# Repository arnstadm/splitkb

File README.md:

# katamaran

Split keyboard with f103

Not prototyped, don't make this

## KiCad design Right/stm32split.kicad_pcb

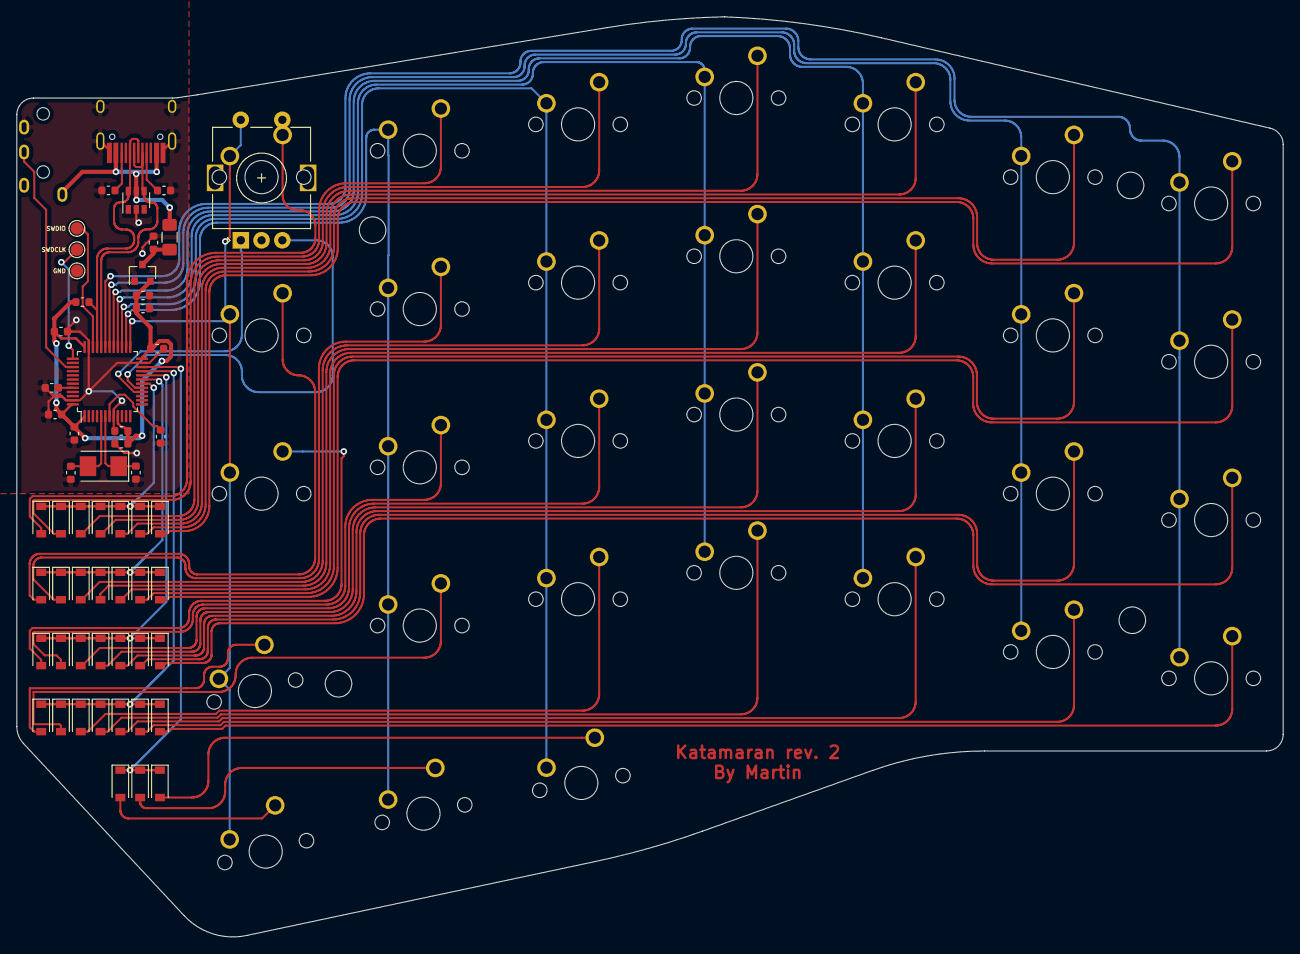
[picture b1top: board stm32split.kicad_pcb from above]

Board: 2 copper layers, 152.4 x 110.7 mm, 88 parts (1 on the bottom side), 58 nets.

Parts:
C3, C6, C7, C8, C9, C11: 100n; C_0603_1608Metric
C4, C5: 20p; C_0603_1608Metric
C10: 1u; C_0603_1608Metric
C12: 10u; C_0603_1608Metric
CVR1, CVR2: 1uF; C_0603_1608Metric
D1, D2, D3, D4, D5, D6, D7, D8, D9, D10, D11, D12, D13, D14, D15, D16, D17, D18, D19, D20, D21, D22, D23, D24, D25, D26, D27, D28, D29, D30, D31: D_Small; D_SOD-123
F1: Fuse_Small; Fuse_1206_3216Metric_Pad1.42x1.75mm_HandSolder
GND: Conn_01x01_Female; TestPoint_Pad_D1.5mm
J1: Conn_01x04; PJ-3200B-4A
R1, R2: 5.1k; R_0603_1608Metric
R3: 1.5k; R_0603_1608Metric
R4: 10k; R_0603_1608Metric
SW1, SW2, SW3, SW4, SW5, SW6, SW7, SW8, SW9, SW10, SW11, SW12, SW13, SW14, SW15, SW16, SW17, SW18, SW19, SW20, SW21, SW22, SW23, SW24, SW25, SW26, SW27, SW28, SW29, SW30, SW31: SW_Push; MXOnly-1U-NoLED
SWDCLK: Conn_01x01_Female; TestPoint_Pad_D1.5mm
SWDIO: Conn_01x01_Female; TestPoint_Pad_D1.5mm
U1: SRV05-4; SOT-23-6
U2: STM32F103CBTx; LQFP-48_7x7mm_P0.5mm
U3: XC6206PxxxMR; SOT-23
USB1: HRO-TYPE-C-31-M-12; HRO-TYPE-C-31-M-12-HandSoldering
Y1: 8MHz; Crystal_SMD_5032-2Pin_5.0x3.2mm

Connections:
+5V: CVR1.1, F1.1, U3.3
BOOT0: R4.1, U2.44
COL0: SW1.1, SW8.1, SW15.1, SW22.1, U2.31
COL1: SW2.1, SW9.1, SW16.1, SW23.1, U2.30
COL2: SW3.1, SW10.1, SW17.1, SW24.1, U2.29
COL3: SW4.1, SW11.1, SW18.1, SW25.1, U2.28
COL4: SW5.1, SW12.1, SW19.1, SW26.1, SW29.1, U2.27
COL5: SW6.1, SW13.1, SW20.1, SW27.1, SW30.1, U2.26
COL6: SW7.1, SW14.1, SW21.1, SW28.1, SW31.1, U2.25
D+: R3.2, U1.6, U2.33, USB1.6, USB1.8
D-: U1.4, U2.32, USB1.5, USB1.7
GND: C3.2, C4.2, C5.2, C6.1, C7.1, C8.1, C9.1, C10.1, C11.1, C12.1, CVR1.2, CVR2.2, GND.1, J1.1, R1.1, R2.1, R4.2, U1.2, U2.8, U2.23, U2.35, U2.47, U3.1, USB1.1, USB1.12, USB1.13
NRST: C3.1, U2.7
unnamed: C4.1, U2.5, Y1.2
unnamed: C5.1, U2.6, Y1.1
unnamed: D1.2, SW1.2
unnamed: D2.2, SW2.2
unnamed: D3.2, SW3.2
unnamed: D4.2, SW4.2
unnamed: D5.2, SW5.2
unnamed: D6.2, SW6.2
unnamed: D7.2, SW7.2
unnamed: D8.2, SW8.2
unnamed: D9.2, SW9.2
unnamed: D10.2, SW10.2
unnamed: D11.2, SW11.2
unnamed: D12.2, SW12.2
unnamed: D13.2, SW13.2
unnamed: D14.2, SW14.2
unnamed: D15.2, SW15.2
unnamed: D16.2, SW16.2
unnamed: D17.2, SW17.2
unnamed: D18.2, SW18.2
unnamed: D19.2, SW19.2
unnamed: D20.2, SW20.2
unnamed: D21.2, SW21.2
unnamed: D22.2, SW22.2
unnamed: D23.2, SW23.2
unnamed: D24.2, SW24.2
unnamed: D25.2, SW25.2
unnamed: D26.2, SW26.2
unnamed: D27.2, SW27.2
unnamed: D28.2, SW28.2
unnamed: D29.2, SW29.2
unnamed: D30.2, SW30.2
unnamed: D31.2, SW31.2
unnamed: R1.2, USB1.4
unnamed: R2.2, USB1.10
ROW0: D1.1, D2.1, D3.1, D4.1, D5.1, D6.1, D7.1, U2.18
ROW1: D8.1, D9.1, D10.1, D11.1, D12.1, D13.1, D14.1, U2.19
ROW2: D15.1, D16.1, D17.1, D18.1, D19.1, D20.1, D21.1, U2.20
ROW3: D22.1, D23.1, D24.1, D25.1, D26.1, D27.1, D28.1, U2.21
ROW4: D29.1, D30.1, D31.1, U2.22
SPLITHANDPIN: J1.2, U2.39
SWDCLK: SWDCLK.1, U2.37
SWDIO: SWDIO.1, U2.34
VBAT: C6.2, C7.2, C8.2, C9.2, C10.2, C11.2, C12.2, CVR2.1, R3.1, U2.1, U2.9, U2.24, U2.36, U2.48, U3.2
VBUS: F1.2, J1.4, U1.5, USB1.2, USB1.11

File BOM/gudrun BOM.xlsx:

Comment | Designator | Footprint | LCSC Part #
1u | C10, CVR1,CVR2 | Capacitor_SMD:C_0603_1608Metric | C15849
10u | C12 | Capacitor_SMD:C_0603_1608Metric | C19702
100n | C3,C6,C7,C8,C9,C11 | Capacitor_SMD:C_0603_1608Metric | C14663
20p | C4,C5 | Capacitor_SMD:C_0603_1608Metric | C1648
BAV70 | D1,D2,D3,D4,D5,D6,D7,D8,D9,D10,D11,D12,D13,D14,D15,D16,D17,D18,D19,D20,D21,D22,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 | Package_TO_SOT_SMD:SOT-23 | C68978
500mA | F1 | Fuse:Fuse_1206_3216Metric_Pad1.42x1.75mm_HandSolder | C369159
HRO-TYPE-C-31-M-12 | J1 | Type-C:HRO-TYPE-C-31-M-12
Conn_01x04_Male | J2 | random-keyboard-parts:JST-SR-4
Conn_01x03_Female | J3 | Connector_PinSocket_1.00mm:PinSocket_1x03_P1.00mm_Vertical
5.1k | R1,R2 | Resistor_SMD:R_0603_1608Metric | C23186
1.5k | R3 | Resistor_SMD:R_0603_1608Metric | C22843
10k | R4 | Resistor_SMD:R_0603_1608Metric | C25804
SRV05-4 | U1 | Package_TO_SOT_SMD:SOT-23-6 | C85364
STM32F103CBTx | U2 | Package_QFP:LQFP-48_7x7mm_P0.5mm | C8304
XC6206P322MR | U3 | Package_TO_SOT_SMD:SOT-23 | C5446
8MHz | Y1 | Crystal:Crystal_SMD_5032-2Pin_5.0x3.2mm | C115962

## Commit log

2020-06-18 pcb files
2020-06-18 added holes
2020-06-18 added top plate
2020-06-18 added bottom plate
2020-06-18 pictures
2020-07-05 new rev
2020-07-05 tracks
2020-07-05 holes
2020-07-06 positioning
2020-07-06 routing
2020-07-06 minor adjustments
2020-07-10 waves and boats
2020-07-10 waves
2020-07-10 readme
2020-07-11 dxf files
2020-07-17 rev 1
2020-11-30 test
2020-11-30 rev2
2020-12-01 cleanup
2020-12-01 changed vbus pin
